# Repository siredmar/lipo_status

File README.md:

# lipo_status
small pcb that indicates the

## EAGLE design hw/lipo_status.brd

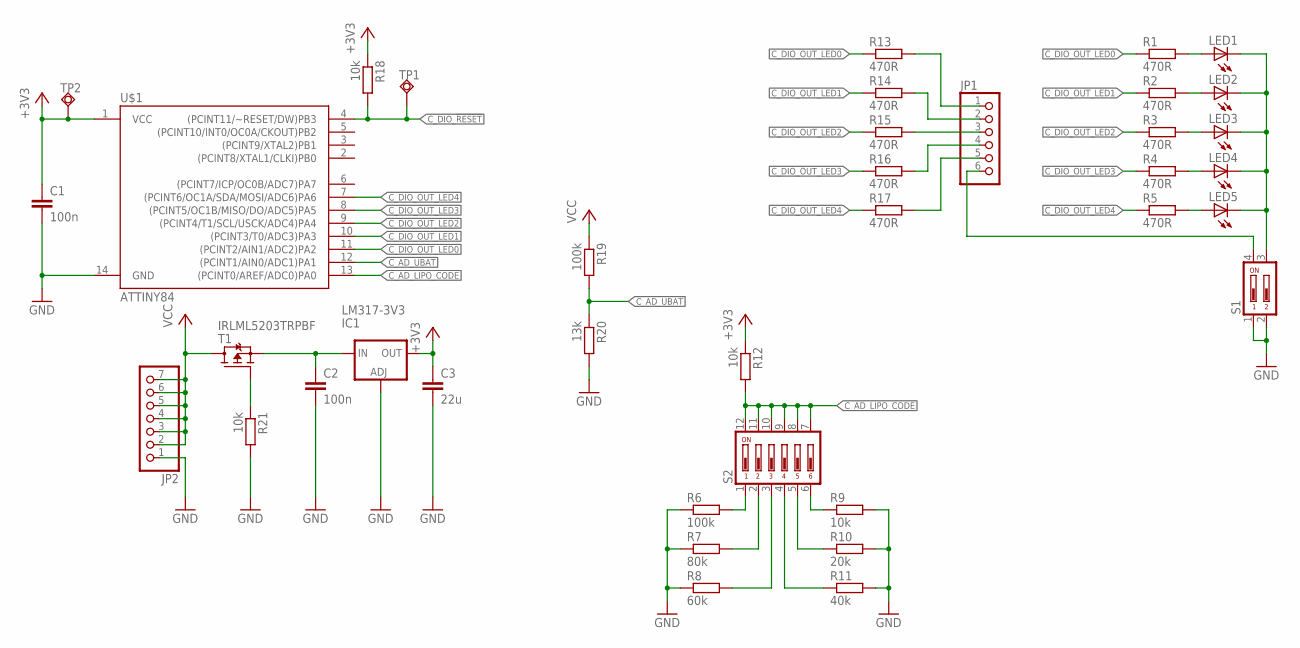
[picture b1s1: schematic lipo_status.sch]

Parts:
C1: 100n; C0603
C2: 100n; C0805
C3: 22u; C0805
IC1: LM317-3V3; SOT223
JP1: PINHD-1X6; 1X06
JP2: PINHD-1X7; 1X07
LED1, LED2, LED3, LED4, LED5: LEDCHIP-LED0805; CHIP-LED0805
R1, R2, R3, R4, R5, R13, R14, R15, R16, R17: 470R; R0603
R6, R19: 100k; R0603
R7: 80k; R0603
R8: 60k; R0603
R9, R12, R18, R21: 10k; R0603
R10: 20k; R0603
R11: 40k; R0603
R20: 13k; R0603
S1: DIP02YL
S2: DIP06YL
T1: IRLML5203TRPBF; SOT23
TP1, TP2: TPSQPAD1-13; P1-13
U$1: ATTINY84; SO14

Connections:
+3V3: C1.1, C3.1, IC1.4 (OUT), R12.1, R18.1, TP2.TP, U$1.1 (VCC)
C_AD_LIPO_CODE: R12.2, S2.7, S2.8, S2.9, S2.10, S2.11, S2.12, U$1.13 ((PCINT0/AREF/ADC0)PA0)
C_AD_UBAT: R19.2, R20.1, U$1.12 ((PCINT1/AIN0/ADC1)PA1)
C_DIO_!RESET: R18.2, TP1.TP, U$1.4 ((PCINT11/~RESET/DW)PB3)
C_DIO_OUT_LED0: R1.1, R13.1, U$1.11 ((PCINT2/AIN1/ADC2)PA2)
C_DIO_OUT_LED1: R2.1, R14.1, U$1.10 ((PCINT3/T0/ADC3)PA3)
C_DIO_OUT_LED2: R3.1, R15.1, U$1.9 ((PCINT4/T1/SCL/USCK/ADC4)PA4)
C_DIO_OUT_LED3: R4.1, R16.1, U$1.8 ((PCINT5/OC1B/MISO/DO/ADC5)PA5)
C_DIO_OUT_LED4: R5.1, R17.1, U$1.7 ((PCINT6/OC1A/SDA/MOSI/ADC6)PA6)
GND: C1.2, C2.2, C3.2, IC1.1 (ADJ), JP2.1, R6.1, R7.1, R8.1, R9.2, R10.2, R11.2, R20.2, R21.2, S1.1, S1.2, U$1.14 (GND)
unnamed: LED1.A, R1.2
unnamed: LED2.A, R2.2
unnamed: LED3.A, R3.2
unnamed: LED4.A, R4.2
unnamed: LED5.A, R5.2
unnamed: R6.2, S2.1
unnamed: R7.2, S2.2
unnamed: R8.2, S2.3
unnamed: R9.1, S2.6
unnamed: R10.1, S2.5
unnamed: R11.1, S2.4
unnamed: JP1.6, S1.4
unnamed: JP1.5, R17.2
unnamed: JP1.4, R16.2
unnamed: JP1.3, R15.2
unnamed: LED1.C, LED2.C, LED3.C, LED4.C, LED5.C, S1.3
unnamed: JP1.2, R14.2
unnamed: JP1.1, R13.2
unnamed: R21.1, T1.1 (G)
unnamed: C2.1, IC1.3 (IN), T1.2 (S)
VCC: JP2.2, JP2.3, JP2.4, JP2.5, JP2.6, JP2.7, R19.1, T1.3 (D)

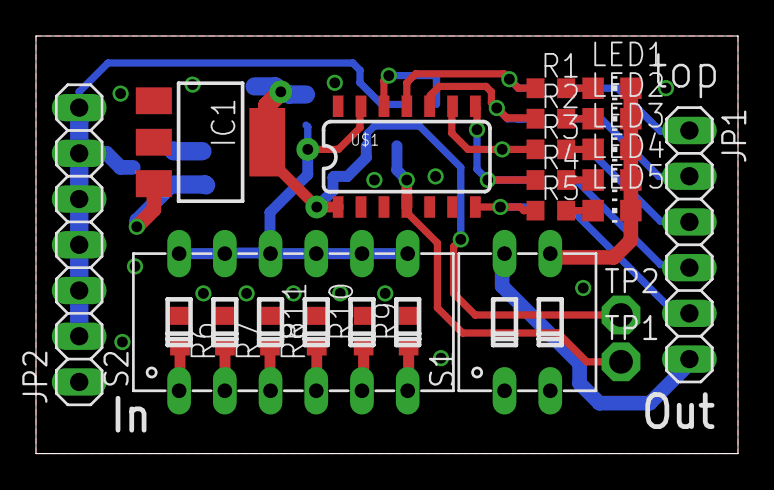
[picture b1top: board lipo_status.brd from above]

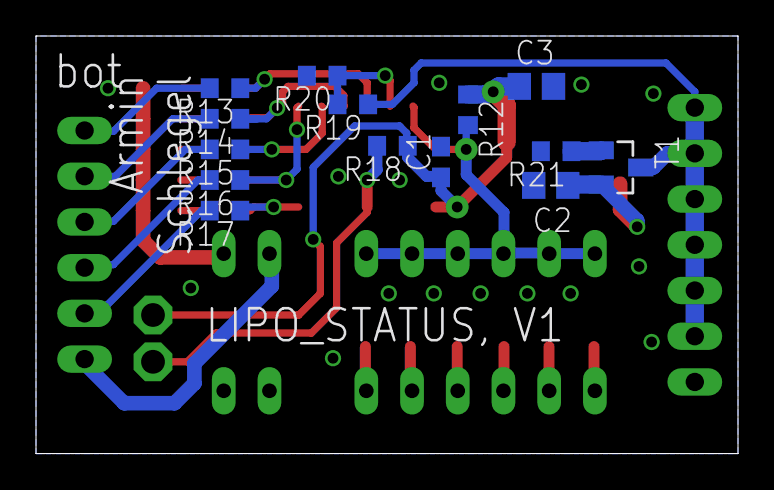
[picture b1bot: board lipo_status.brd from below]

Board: 2 copper layers, 39.0 x 23.2 mm, 38 parts (14 on the bottom side), 31 nets.

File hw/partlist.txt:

Partlist

Exported from lipo_status.brd at 4/9/15 7:17 AM

EAGLE Version 6.6.0 Copyright (c) 1988-2014 CadSoft

Assembly variant: 

Part     Value          Package      Library            Position (mm)         Orientation

C1       100n           C0603        rcl                (16.5 16.2)           MR90
C2       100n           C0805        rcl                (10.4 14.9)           MR180
C3       22u            C0805        rcl                (11.2 20.4)           MR0
IC1      LM317-3V3      SOT223       v-reg              (9.7 17.3)            R270
JP1                     1X06         pinhead            (36.3 11.6)           R270
JP2                     1X07         pinhead            (2.4 11.6)            R90
LED1                    CHIP-LED0805 led                (32 20.3)             R270
LED2                    CHIP-LED0805 led                (32 18.6)             R270
LED3                    CHIP-LED0805 led                (32 16.9)             R270
LED4                    CHIP-LED0805 led                (32 15.2)             R270
LED5                    CHIP-LED0805 led                (32 13.5)             R270
R1       470R           R0603        rcl                (28.6 20.3)           R0
R2       470R           R0603        rcl                (28.6 18.6)           R0
R3       470R           R0603        rcl                (28.6 16.9)           R0
R4       470R           R0603        rcl                (28.6 15.2)           R0
R5       470R           R0603        rcl                (28.6 13.5)           R0
R6       100k           R0603        rcl                (8 6.8)               R270
R7       80k            R0603        rcl                (10.5 6.8)            R270
R8       60k            R0603        rcl                (13 6.8)              R270
R9       10k            R0603        rcl                (20.7 6.8)            R90
R10      20k            R0603        rcl                (18.2 6.8)            R90
R11      40k            R0603        rcl                (15.6 6.8)            R90
R12      10k            R0603        rcl                (15 19.1)             MR270
R13      470R           R0603        rcl                (28.5 20.3)           MR180
R14      470R           R0603        rcl                (28.5 18.6)           MR180
R15      470R           R0603        rcl                (28.5 16.9)           MR180
R16      470R           R0603        rcl                (28.5 15.2)           MR180
R17      470R           R0603        rcl                (28.5 13.5)           MR180
R18      10k            R0603        rcl                (19.2 17.1)           MR180
R19      100k           R0603        rcl                (21.4 19.4)           MR180
R20      13k            R0603        rcl                (23.1 21)             MR180
R21      10k            R0603        rcl                (10.1 16.8)           MR180
S1                      DIP02YL      switch-dil         (27.3 7.3)            R0
S2                      DIP06YL      switch-dil         (14.3 7.3)            R0
T1       IRLML5203TRPBF SOT23        SchlegelAr_Master  (6.5 15.9)            MR270
TP1      TPSQPAD1-13    P1-13        testpad            (32.5 5.1)            R0
TP2      TPSQPAD1-13    P1-13        testpad            (32.5 7.7)            R0
U$1      ATTINY84       SO14         SparkFun-DigitalIC (20.6 16.5)           R0

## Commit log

2015-03-02 initial sw version, tested on arduino
2015-03-06 removed tracking of eagle backup files\nadapted SW\nadapted schematic and layout
2015-03-07 added gerber files
2015-03-07 added attint84 software, first shot
2015-03-07 added led output
2015-03-07 corrected switching ranges
2015-04-09 partlist and picture of pcb added

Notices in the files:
parts and their libraries:
SparkFun-DigitalIC: Licensing: Creative Commons ShareAlike 4.0 International - https://creativecommons.org/licenses/by-sa/4.0
